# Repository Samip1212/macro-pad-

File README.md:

ESP32-S3 MACRO PAD
 
Its a  simple 6key USB macro pad made with an ESP32-S3 and an OLED display.
The display shows "Connected" or "Disconnected" (USB status).
 
KEYS
  Key 1 (GPIO 18)  Copy
  Key 2 (GPIO 35)  Paste
  Key 3 (GPIO 21)  Cut
  Key 4 (GPIO 38)  Open YouTube
  Key 5 (GPIO 37)  Open Safari
  Key 6 (GPIO 36)  Close tab
 
DISPLAY
  SDA -> GPIO 45
  SCL -> GPIO 46
 
WIRING
  Each switch goes between its GPIO pin and GND,3v3.
 
SETUP
  1. Install the Arduino IDE and the ESP32 board package.
  2. Install libraries: Adafruit SSD1306 and Adafruit GFX Library.
  3. In Tools, set:
       Board: ESP32S3 Dev Module
       USB Mode: USB-OTG (TinyUSB)
       USB CDC On Boot: Disabled
  4. Open macropad.ino, then upload it to the board.
  5. Plug the board into your computer by USB.

 For window user 
  - Shortcuts use the Command key (Mac).
    For Windows, change KEY_LEFT_GUI to KEY_LEFT_CTRL in the code.

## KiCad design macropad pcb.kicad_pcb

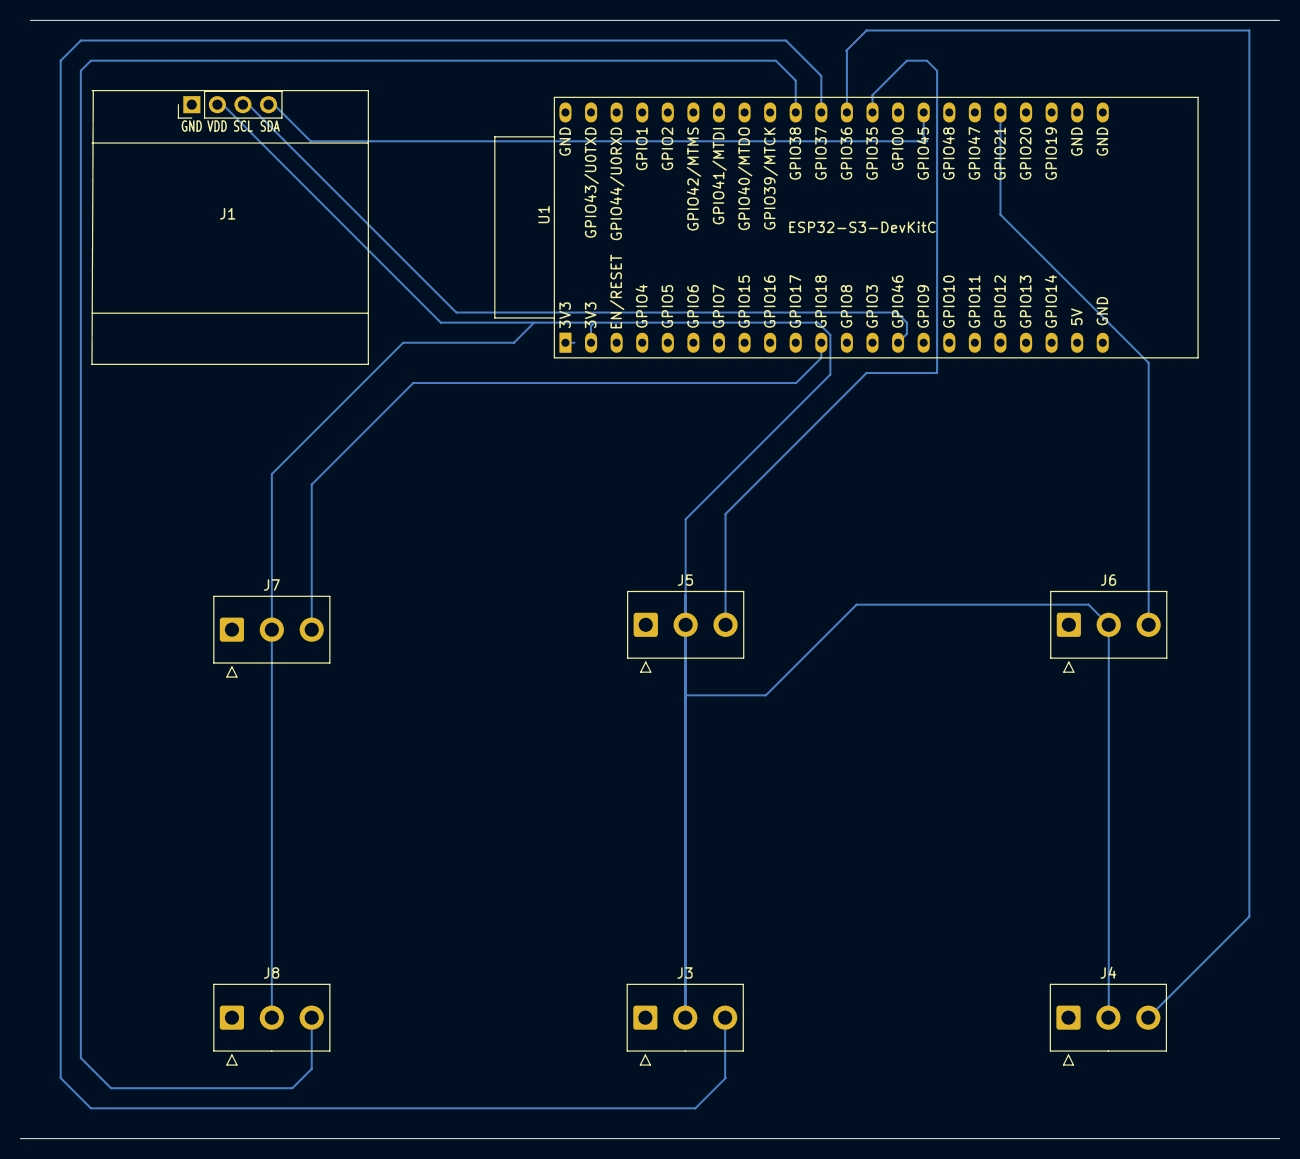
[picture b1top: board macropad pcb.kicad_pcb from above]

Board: 2 copper layers, 125.0 x 111.0 mm, 8 parts (0 on the bottom side), 10 nets.

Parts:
J1: Conn_01x04_Pin; Display_128x64_096_I2C
J3, J4, J5, J6, J7, J8: Conn_01x03_Socket; TE_826576-3_1x03_P3.96mm_Vertical
U1: ESP32-S3-DevKitC

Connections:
/3v: J1.2, J3.2, J4.2, J5.2, J6.2, J7.2, J8.2, U1.1 (3V3), U1.2 (3V3)
/a: J8.3, U1.35 (GPIO38)
/b: J3.3, U1.34 (GPIO37)
/c: J4.3, U1.33 (GPIO36)
/d: J5.3, U1.32 (GPIO35)
/e: J6.3, U1.27 (GPIO21)
/f: J7.3, U1.11 (GPIO18/ADC2_CH7)
/q: J1.3, U1.14 (GPIO46)
/w: J1.4, U1.30 (GPIO45)
GND: J1.1, J3.1, J4.1, J5.1, J6.1, J7.1, J8.1, U1.22 (GND), U1.23 (GND), U1.24 (GND), U1.44 (GND)
